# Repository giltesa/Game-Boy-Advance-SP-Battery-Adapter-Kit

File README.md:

# Game Boy Advance SP Battery Adapter Kit

Once your **Game Boy Advance SP battery** has gone bad, and you start to look for a replacement you will see it is impossible to find original batteries since they expire if you do not keep charged with a minimum level of charge.

Compatible batteries may be an alternative. However, some manufacturers  may lie with the real capacity or their quality is not good enough.

If you have changed the screen for a IPS screen, or the [charging port for a USB-C port](https://shop.giltesa.com/product/game-boy-advance-sp-usb-c-kit-centered/ "charging port for a USB-C port"). I am sure you will also want to replace the battery and make your GBA SP perfect. This kit helps you to install any li-ion battery, however the best option is the [603048](https://www.aliexpress.com/item/4001084877373.html? "603048") which has 900mAh, that is 300mAh more than the original!

## Would you like it?

https://shop.giltesa.com/product/game-boy-advance-sp-battery-adapter-kit

## More

- [giltesa.com](https://giltesa.com "giltesa.com")
- [twitter.com](https://twitter.com/giltesa/status/1503669454852481024 "twitter.com")

## License

This project is licensed under a **Creative Commons** license:
**[Attribution-NonCommercial-ShareAlike 4.0 International (CC BY-NC-SA 4.0) ](https://creativecommons.org/licenses/by-nc-sa/4.0/)**

Check the [LICENSE.md](LICENSE.md) for more information.

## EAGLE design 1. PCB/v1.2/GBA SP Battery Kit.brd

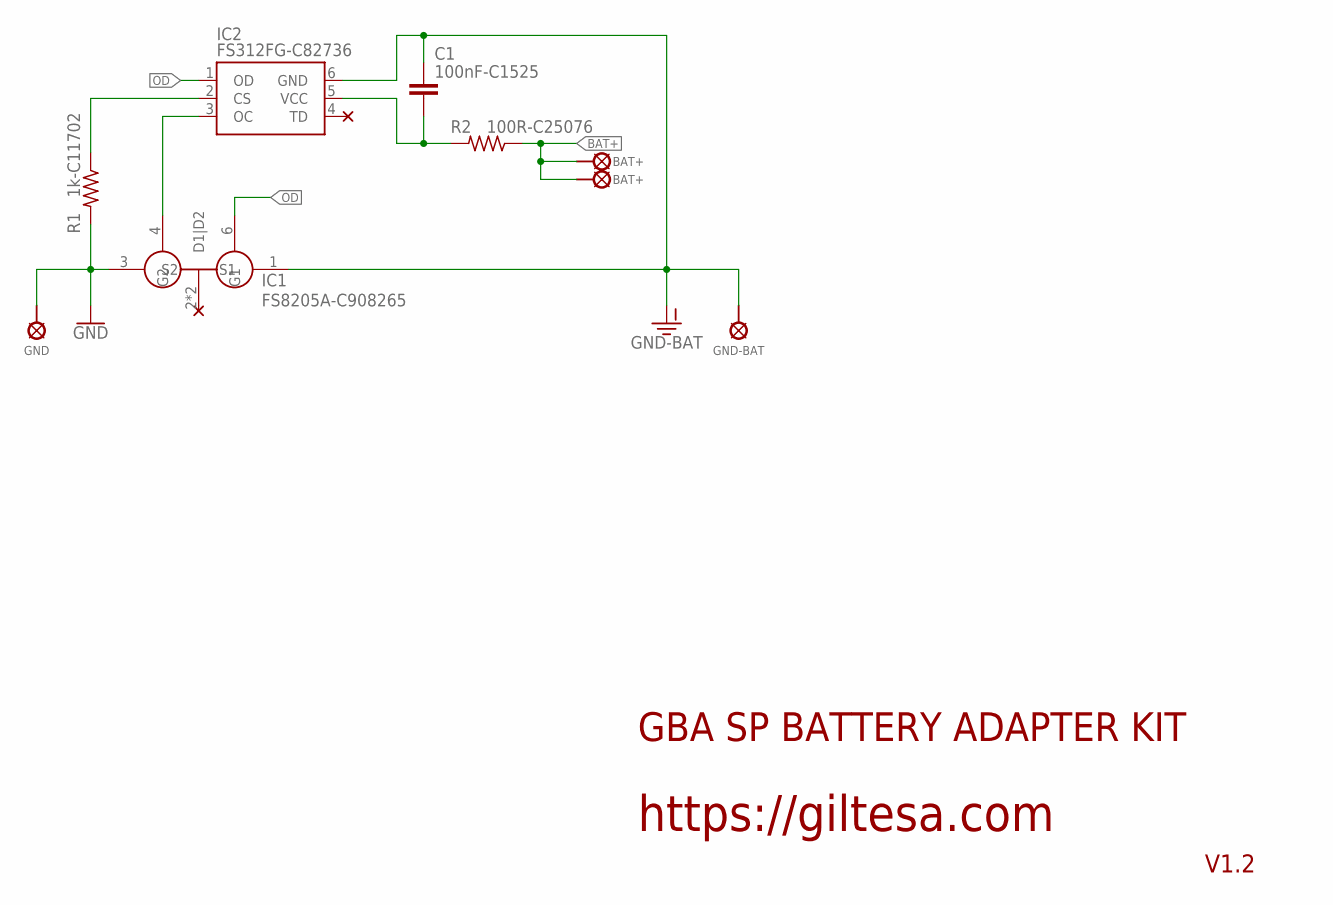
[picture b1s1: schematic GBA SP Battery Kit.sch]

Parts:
C1: 100nF-C1525; C0402_S
IC1: FS8205A-C908265; SOT-23-6_GBASP
IC2: FS312FG-C82736; SOT-23-6_GBASP_SHORT
R1: 1k-C11702; R0402
R2: 100R-C25076; R0402
U$2: BAT+; BATTERY_SOLDER_PAD
U$4: GND-BAT; BATTERY_SOLDER_PAD
U$5: GND; BATTERY_SOLDER_PAD_GBASP
U$9: BAT+; BATTERY_SOLDER_PAD_GBASP

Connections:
BAT+: R2.1, U$2.1, U$9.1
GND: IC1.3 (S2), R1.2, U$5.1
GND-BAT: C1.1, IC1.1 (S1), IC2.6 (GND), U$4.1
unnamed: IC2.2 (CS), R1.1
unnamed: IC1.4 (G2), IC2.3 (OC)
OD: IC1.6 (G1), IC2.1 (OD)
VCC-DW: C1.2, IC2.5 (VCC), R2.2

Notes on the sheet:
https://giltesa.com
V1.2
GBA SP BATTERY ADAPTER KIT

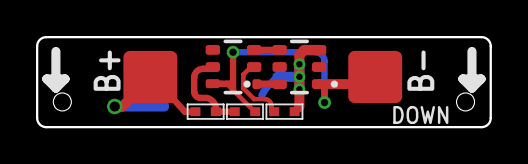
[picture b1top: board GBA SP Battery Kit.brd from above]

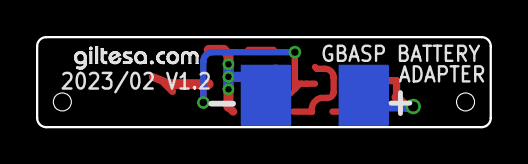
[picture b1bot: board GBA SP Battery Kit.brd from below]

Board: 2 copper layers, 25.2 x 5.0 mm, 10 parts (3 on the bottom side), 7 nets.

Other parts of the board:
U$28: GILTESA.COM_MASK_7MM

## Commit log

2023-02-12 First push
2023-02-12 v1.0
2023-02-12 v1.1
2023-02-12 v1.2
2023-03-23 no message

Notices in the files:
parts and their libraries:
SparkFun: Licensing: CC v3.0 Share-Alike You are welcome to use this library for commercial purposes.
SparkFun-PowerSymbols: Licensing: Creative Commons ShareAlike 4.0 International - https://creativecommons.org/licenses/by-sa/4.0
